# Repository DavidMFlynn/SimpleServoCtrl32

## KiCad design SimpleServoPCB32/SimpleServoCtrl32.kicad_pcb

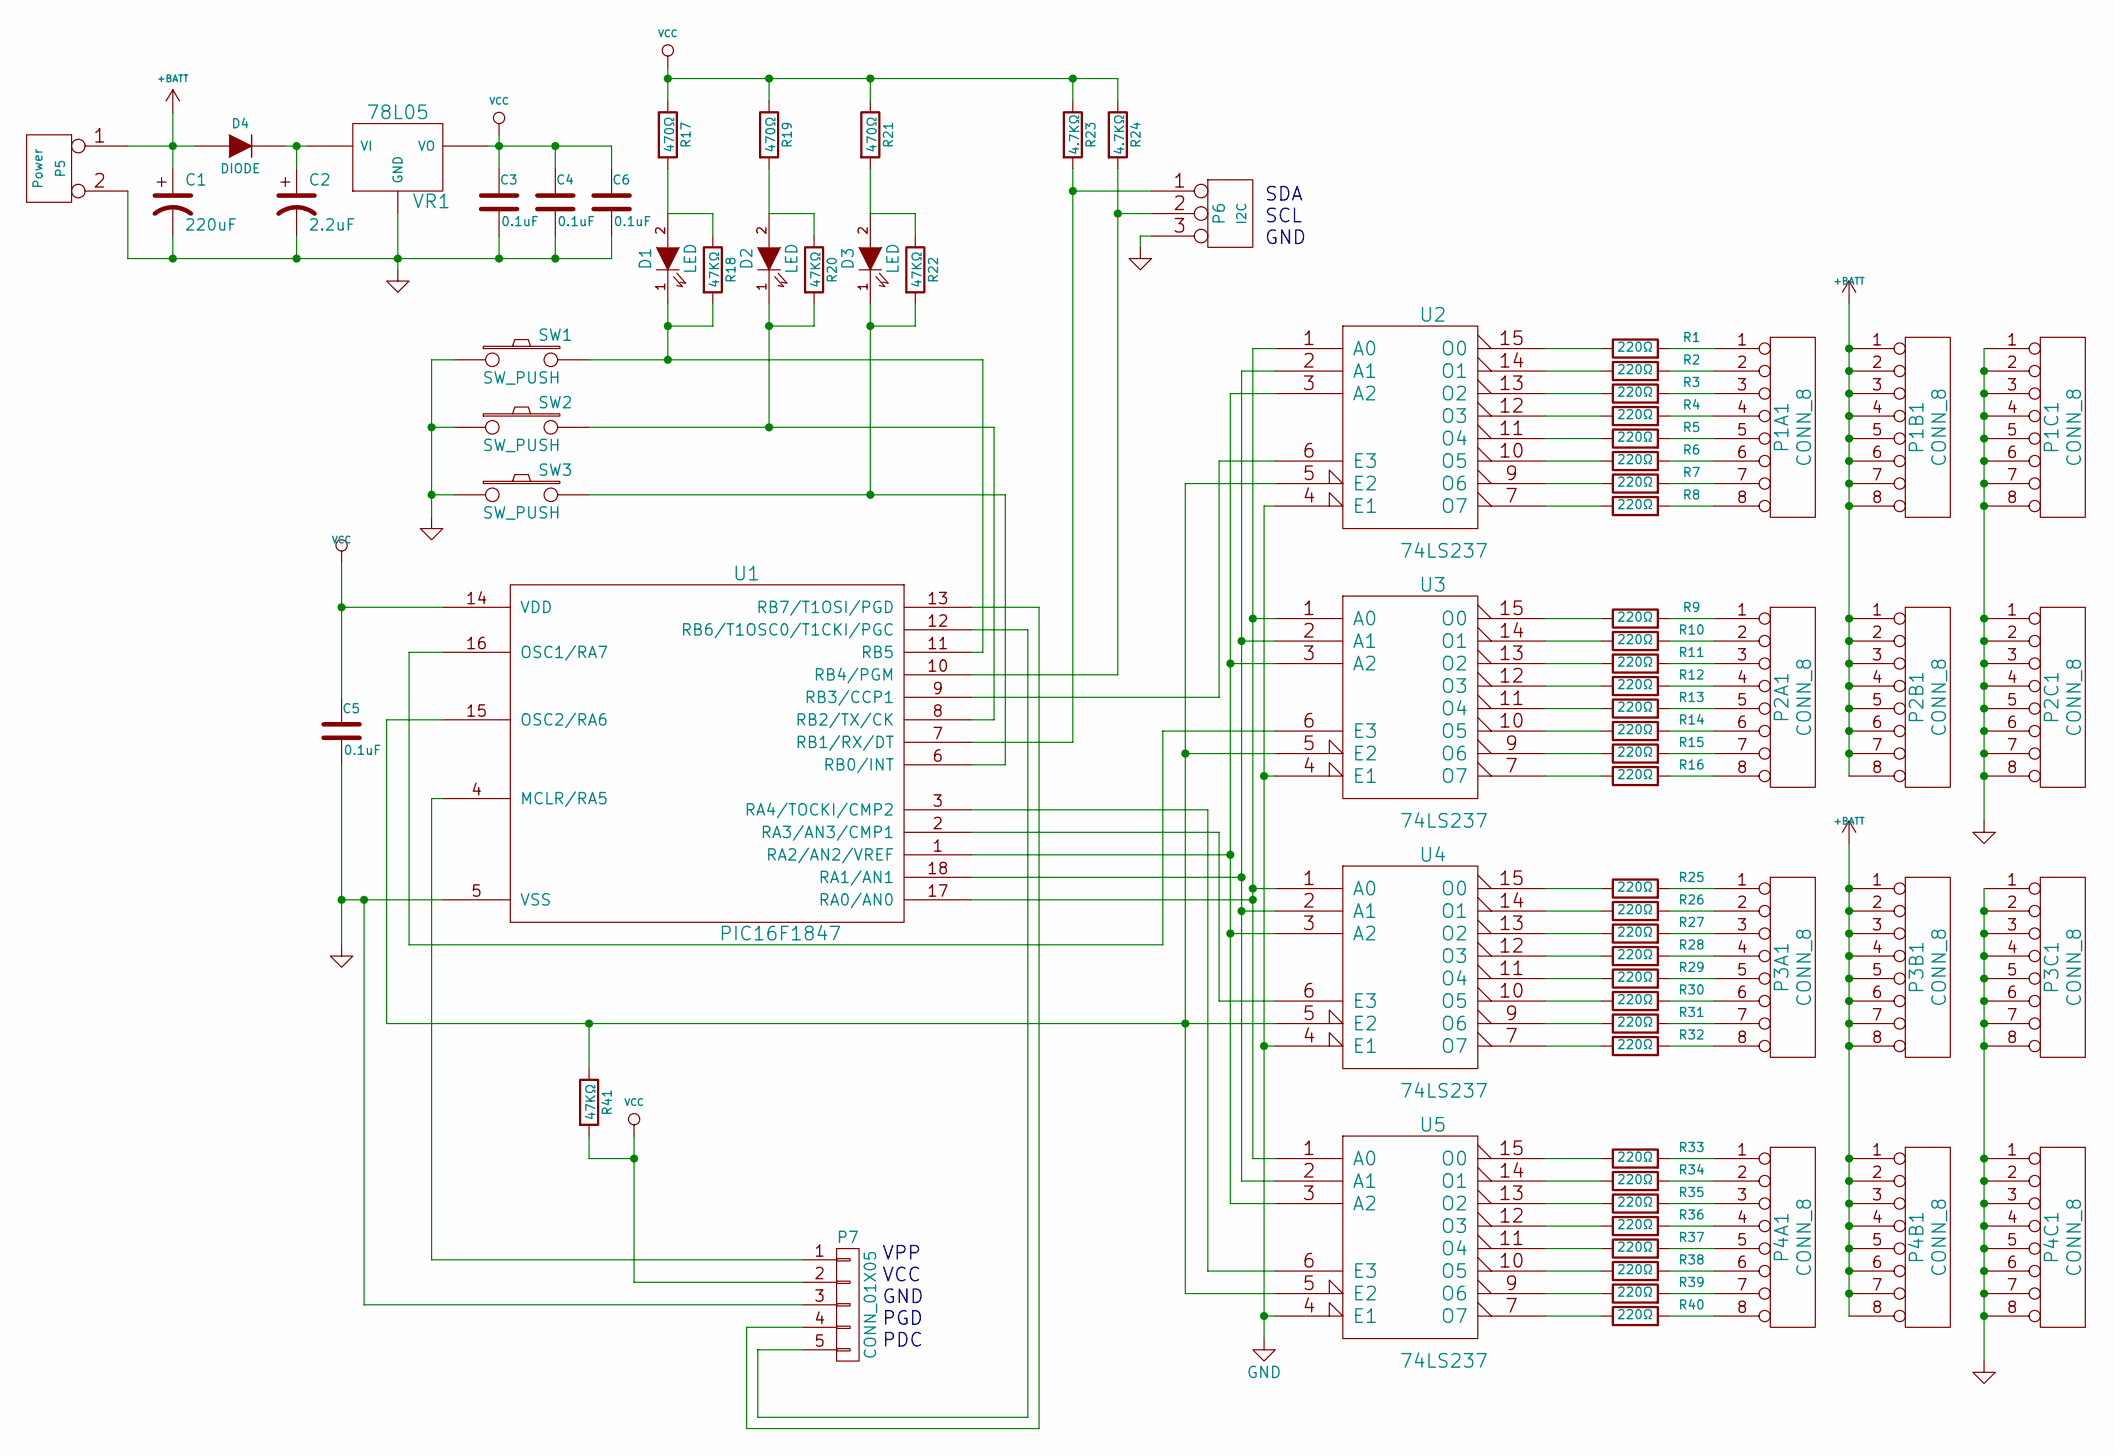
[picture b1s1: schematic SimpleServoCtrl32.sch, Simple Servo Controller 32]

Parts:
C1: 220uF; Elko_vert_20x10mm_RM5_CopperClear
C2: 2.2uF; Elko_vert_11x5mm_RM2.5
C3, C4, C5, C6: 0.1uF; C_0805_HandSoldering
D1, D2, D3: LED; LED-1206
D4: DIODE; SMD-2010_Pol
P1A1, P1B1, P1C1, P2A1, P2B1, P2C1, P3A1, P3B1, P3C1, P4A1, P4B1, P4C1: CONN_8; Pin_Header_Straight_1x08
P5: Power; bornier2
P6: I2C; bornier3
P7: CONN_01X05; Pin_Header_Straight_1x05
R1, R2, R3, R4, R5, R6, R7, R8, R9, R10, R11, R12, R13, R14, R15, R16, R25, R26, R27, R28, R29, R30, R31, R32, R33, R34, R35, R36, R37, R38, R39, R40: 220Ω; R_0805_HandSoldering
R17, R19, R21: 470Ω; R_0805_HandSoldering
R18, R20, R22, R41: 47KΩ; R_0805_HandSoldering
R23, R24: 4.7KΩ; R_0805_HandSoldering
SW1, SW2, SW3: SW_PUSH; SW_SPST_PTS645
U1: PIC16F1847; DIP-18__300
U2, U3, U4, U5: 74LS237; SOIC-16_3.9x9.9mm_Pitch1.27mm
VR1: 78L05; TO-263

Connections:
+BATT: C1.1, D4.1 (A), P1B1.1, P1B1.2, P1B1.3, P1B1.4, P1B1.5, P1B1.6, P1B1.7, P1B1.8, P2B1.1, P2B1.2, P2B1.3, P2B1.4, P2B1.5, P2B1.6, P2B1.7, P2B1.8, P3B1.1, P3B1.2, P3B1.3, P3B1.4, P3B1.5, P3B1.6, P3B1.7, P3B1.8, P4B1.1, P4B1.2, P4B1.3, P4B1.4, P4B1.5, P4B1.6, P4B1.7, P4B1.8, P5.1
GND: C1.2, C2.2, C3.2, C4.2, C5.2, C6.2, P1C1.1, P1C1.2, P1C1.3, P1C1.4, P1C1.5, P1C1.6, P1C1.7, P1C1.8, P2C1.1, P2C1.2, P2C1.3, P2C1.4, P2C1.5, P2C1.6, P2C1.7, P2C1.8, P3C1.1, P3C1.2, P3C1.3, P3C1.4, P3C1.5, P3C1.6, P3C1.7, P3C1.8, P4C1.1, P4C1.2, P4C1.3, P4C1.4, P4C1.5, P4C1.6, P4C1.7, P4C1.8, P5.2 (PM), P6.3, P7.3, SW1.1, SW2.1, SW3.1, U1.5 (VSS), U2.4 (E1), U2.8 (GND), U3.4 (E1), U3.8 (GND), U4.4 (E1), U4.8 (GND), U5.4 (E1), U5.8 (GND), VR1.GND
unnamed: C2.1, D4.2 (K), VR1.VI
unnamed: D1.1 (K), R18.2, SW1.2, U1.11 (RB5)
unnamed: D1.2 (A), R17.2, R18.1
unnamed: D2.1 (K), R20.2, SW2.2, U1.8 (RB2/TX/CK)
unnamed: D2.2 (A), R19.2, R20.1
unnamed: D3.1 (K), R22.2, SW3.2, U1.6 (RB0/INT)
unnamed: D3.2 (A), R21.2, R22.1
unnamed: P1A1.1, R1.2
unnamed: P1A1.2, R2.2
unnamed: P1A1.3, R3.2
unnamed: P1A1.4, R4.2
unnamed: P1A1.5, R5.2
unnamed: P1A1.6, R6.2
unnamed: P1A1.7, R7.2
unnamed: P1A1.8, R8.2
unnamed: P2A1.1, R9.2
unnamed: P2A1.2, R10.2
unnamed: P2A1.3, R11.2
unnamed: P2A1.4, R12.2
unnamed: P2A1.5, R13.2
unnamed: P2A1.6, R14.2
unnamed: P2A1.7, R15.2
unnamed: P2A1.8, R16.2
unnamed: P3A1.1, R25.2
unnamed: P3A1.2, R26.2
unnamed: P3A1.3, R27.2
unnamed: P3A1.4, R28.2
unnamed: P3A1.5, R29.2
unnamed: P3A1.6, R30.2
unnamed: P3A1.7, R31.2
unnamed: P3A1.8, R32.2
unnamed: P4A1.1, R33.2
unnamed: P4A1.2, R34.2
unnamed: P4A1.3, R35.2
unnamed: P4A1.4, R36.2
unnamed: P4A1.5, R37.2
unnamed: P4A1.6, R38.2
unnamed: P4A1.7, R39.2
unnamed: P4A1.8, R40.2
unnamed: P6.1, R23.2, U1.7 (RB1/RX/DT)
unnamed: P6.2 (PM), R24.2, U1.10 (RB4/PGM)
unnamed: P7.1, U1.4 (MCLR/RA5)
unnamed: P7.4, U1.13 (RB7/T1OSI/PGD)
unnamed: P7.5, U1.12 (RB6/T1OSC0/T1CKI/PGC)
unnamed: R1.1, U2.15 (O0)
unnamed: R2.1, U2.14 (O1)
unnamed: R3.1, U2.13 (O2)
unnamed: R4.1, U2.12 (O3)
unnamed: R5.1, U2.11 (O4)
unnamed: R6.1, U2.10 (O5)
unnamed: R7.1, U2.9 (O6)
unnamed: R8.1, U2.7 (O7)
unnamed: R9.1, U3.15 (O0)
unnamed: R10.1, U3.14 (O1)
unnamed: R11.1, U3.13 (O2)
unnamed: R12.1, U3.12 (O3)
unnamed: R13.1, U3.11 (O4)
unnamed: R14.1, U3.10 (O5)
unnamed: R15.1, U3.9 (O6)
unnamed: R16.1, U3.7 (O7)
unnamed: R25.1, U4.15 (O0)
unnamed: R26.1, U4.14 (O1)
unnamed: R27.1, U4.13 (O2)
unnamed: R28.1, U4.12 (O3)
unnamed: R29.1, U4.11 (O4)
unnamed: R30.1, U4.10 (O5)
unnamed: R31.1, U4.9 (O6)
unnamed: R32.1, U4.7 (O7)
unnamed: R33.1, U5.15 (O0)
unnamed: R34.1, U5.14 (O1)
unnamed: R35.1, U5.13 (O2)
unnamed: R36.1, U5.12 (O3)
unnamed: R37.1, U5.11 (O4)
unnamed: R38.1, U5.10 (O5)
unnamed: R39.1, U5.9 (O6)
unnamed: R40.1, U5.7 (O7)
unnamed: R41.1, U1.15 (OSC2/RA6), U2.5 (E2), U3.5 (E2), U4.5 (E2), U5.5 (E2)
unnamed: U1.1 (RA2/AN2/VREF), U2.3 (A2), U3.3 (A2), U4.3 (A2), U5.3 (A2)
unnamed: U1.2 (RA3/AN3/CMP1), U4.6 (E3)
unnamed: U1.3 (RA4/TOCKI/CMP2), U5.6 (E3)
unnamed: U1.9 (RB3/CCP1), U2.6 (E3)
unnamed: U1.16 (OSC1/RA7), U3.6 (E3)
unnamed: U1.17 (RA0/AN0), U2.1 (A0), U3.1 (A0), U4.1 (A0), U5.1 (A0)
unnamed: U1.18 (RA1/AN1), U2.2 (A1), U3.2 (A1), U4.2 (A1), U5.2 (A1)
VCC: C3.1, C4.1, C5.1, C6.1, P7.2, R17.1, R19.1, R21.1, R23.1, R24.1, R41.2, U1.14 (VDD), U2.16 (VCC), U3.16 (VCC), U4.16 (VCC), U5.16 (VCC), VR1.VO

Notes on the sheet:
SDA SCL GND
VPP VCC GND PGD PDC

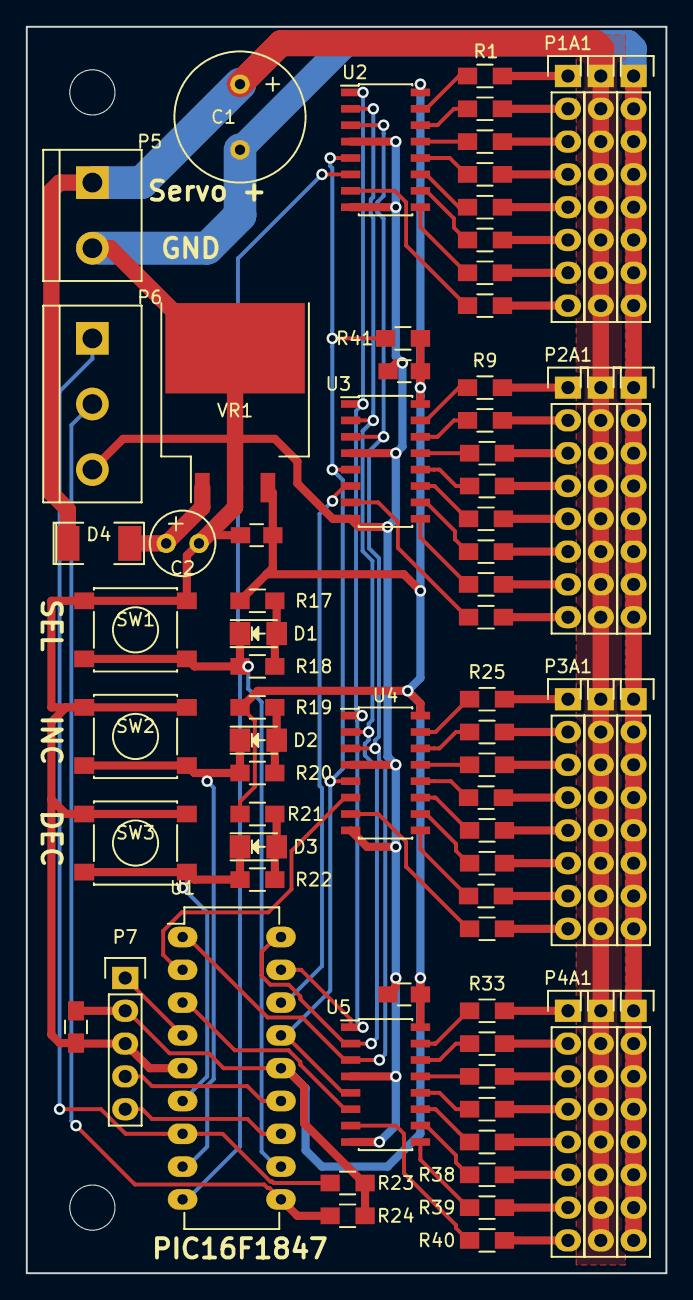
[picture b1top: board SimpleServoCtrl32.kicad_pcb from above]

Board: 2 copper layers, 49.5 x 96.5 mm, 77 parts (0 on the bottom side), 87 nets.

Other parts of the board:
H1, H2: MountingHole_3-5mm

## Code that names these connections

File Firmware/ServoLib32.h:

;====================================================================================================
; PIC16F1847 on SimpleServo16 PCB
;
;   Pin 1 (RA2/AN2) Address A2 (output)
;   Pin 2 (RA3/AN3) Enable Servos 0..7 (active low output)
;   Pin 3 (RA4/AN4) Enable Servos 8..15 (active low output)
;   Pin 4 (RA5/MCLR*) N.C.
;   Pin 5 (GND) Ground
;   Pin 6 (RB0) SW3/LED3 (Active Low Input/Output)
;   Pin 7 (RB1/AN11/SDA1) I2C Data
;   Pin 8 (RB2/AN10/RX) SW2/LED2 (Active Low Input/Output)
;   Pin 9 (RB3/CCP1) Pulse output for Servos 0..7
;
;   Pin 10 (RB4/AN8/SLC1) I2C Clock
;   Pin 11 (RB5/AN7)  SW1/LED1 (Active Low Input/Output)(System LED)
;   Pin 12 (RB6/AN5/CCP2) N.C.
;   Pin 13 (RB7/AN6) N.C.
;   Pin 14 (Vcc) +5 volts
;   Pin 15 (RA6) N.C.
;   Pin 16 (RA7/CCP2) Pulse output for Servos 8..15
;   Pin 17 (RA0) Address A0 (output)
;   Pin 18 (RA1) Address A1 (output)
;
;====================================================================================================
; Constants:
;
DefaultMaxSpeed	EQU	0x30	;1uS/20mS^2
DefaultAccel	EQU	0x01
DefaultSFlags	EQU	b'00100010'	;In Position
;
CCPCON_Clr	EQU	b'00001001'	;Clear output on match
CCPCON_Set	EQU	b'00001000'	;Set output on match
CCPCON_Int	EQU	b'00001010'	;Interupt only on match
;
kCenterPulseWidth	EQU	d'3000'	;1500uS
kMinPulseWidth	EQU	d'1800'	;900uS
kMaxPulseWidth	EQU	d'4200'	;2100uS
kServoDwellTimeA	EQU	d'4500'	;Address Change time 2250uS
kServoAddrTime	EQU	d'500'	;250uS
kServoDwellTime	EQU	d'5000'	;2.5mS/Channel
;
;================================================================================================
;  Bank3 Ram 1A0h-1EFh 80 Bytes
;
Bank3_Vars	udata	0x1A0
ServoMaxSpeed0_7	res	.8	;0=no Accel, 1..255 counts/20mS
ServoMaxSpeed8_15	res	.8
ServoAccelValue0_7	res	.8	;1..8 counts/20mS squared
ServoAccelValue8_15	res	.8
ServoCurSpeed0_7	res	.8	;0=Stopped, MSb=Direction, 1..127
ServoCurSpeed8_15	res	.8
;
;================================================================================================
;  Bank4 Ram 220h-26Fh 80 Bytes
;
Bank4_Vars	udata	0x220
CMDServoIDX	res	1	;0..15, used by IdleServos
CMDSigTime0_7	res	.16	;Commanded position
CMDSigTime8_15	res	.16
MinTime0_7	res	.16	;Minimum pulse time (900uS=1800)
MinTime8_15	res	.16	;Minimum pulse time (900uS=1800)
;
;================================================================================================
;  Bank5 Ram 2A0h-2EFh 80 Bytes
;
Bank5_Vars	udata	0x2A0
ServoIDX	res	1	;Index 0..7
ServoCtlFlags	res	1
; Flag bits, ToDo at Next ISR:
CyclePulseStart	EQU	0	;Start cycle banks 1 and 2
CyclePulseEnd1	EQU	2	;End pulse, begin dwell
CyclePulseEnd2	EQU	3	; Set when a pulse is started.
AddrChngDwell	EQU	4	;dwell 100uS , change address
;
ServoFlags	res	.8	;4 bits per servo
; Flag bits
ValueSentFlag0_7	EQU	0
InPositionFlag0_7	EQU	1
ServoOnBit0_7	EQU	2
MovingFWD0_7	EQU	3
ValueSentFlag8_15	EQU	4
InPositionFlag8_15	EQU	5
ServoOnBit8_15	EQU	6
MovingFWD8_15	EQU	7
;
CalcdDwell	res	1	;scratch var
CalcdDwellH	res	1
SigOutTime0_7	res	.16	;Current position
SigOutTime8_15	res	.16
DwellTime0_7	res	.16	;Next dwell time
DwellTime8_15	res	.16
;
;================================================================================================
;  Bank6 Ram 320h-26Fh 80 Bytes
;
Bank6_Vars	udata	0x320
ServoFlags2	res	.8	;4 bits per servo
; Flag bits
AccelComplete0_7	EQU	0
AccelComplete8_15	EQU	4
MaxTime0_7	res	.16	;Maximum pulse time (2100uS=4200)
MaxTime8_15	res	.16	;Maximum pulse time (2100uS=4200)
AccelRampLen0_7	res	.16
AccelRampLen8_15	res	.16
;
;=========================================================================================
;

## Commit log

2015-11-12 PCB is here, firmware is next
2015-11-16 Getting organized

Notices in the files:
SimpleServoPCB32/SimpleServoCtrl32.kicad_pcb:
GPL v2
SimpleServoPCB32/SimpleServoCtrl32.sch:
OSH GPL 2
